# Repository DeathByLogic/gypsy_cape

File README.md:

# gypsy_cape
BeagleBone cape for the Gypsy robot.

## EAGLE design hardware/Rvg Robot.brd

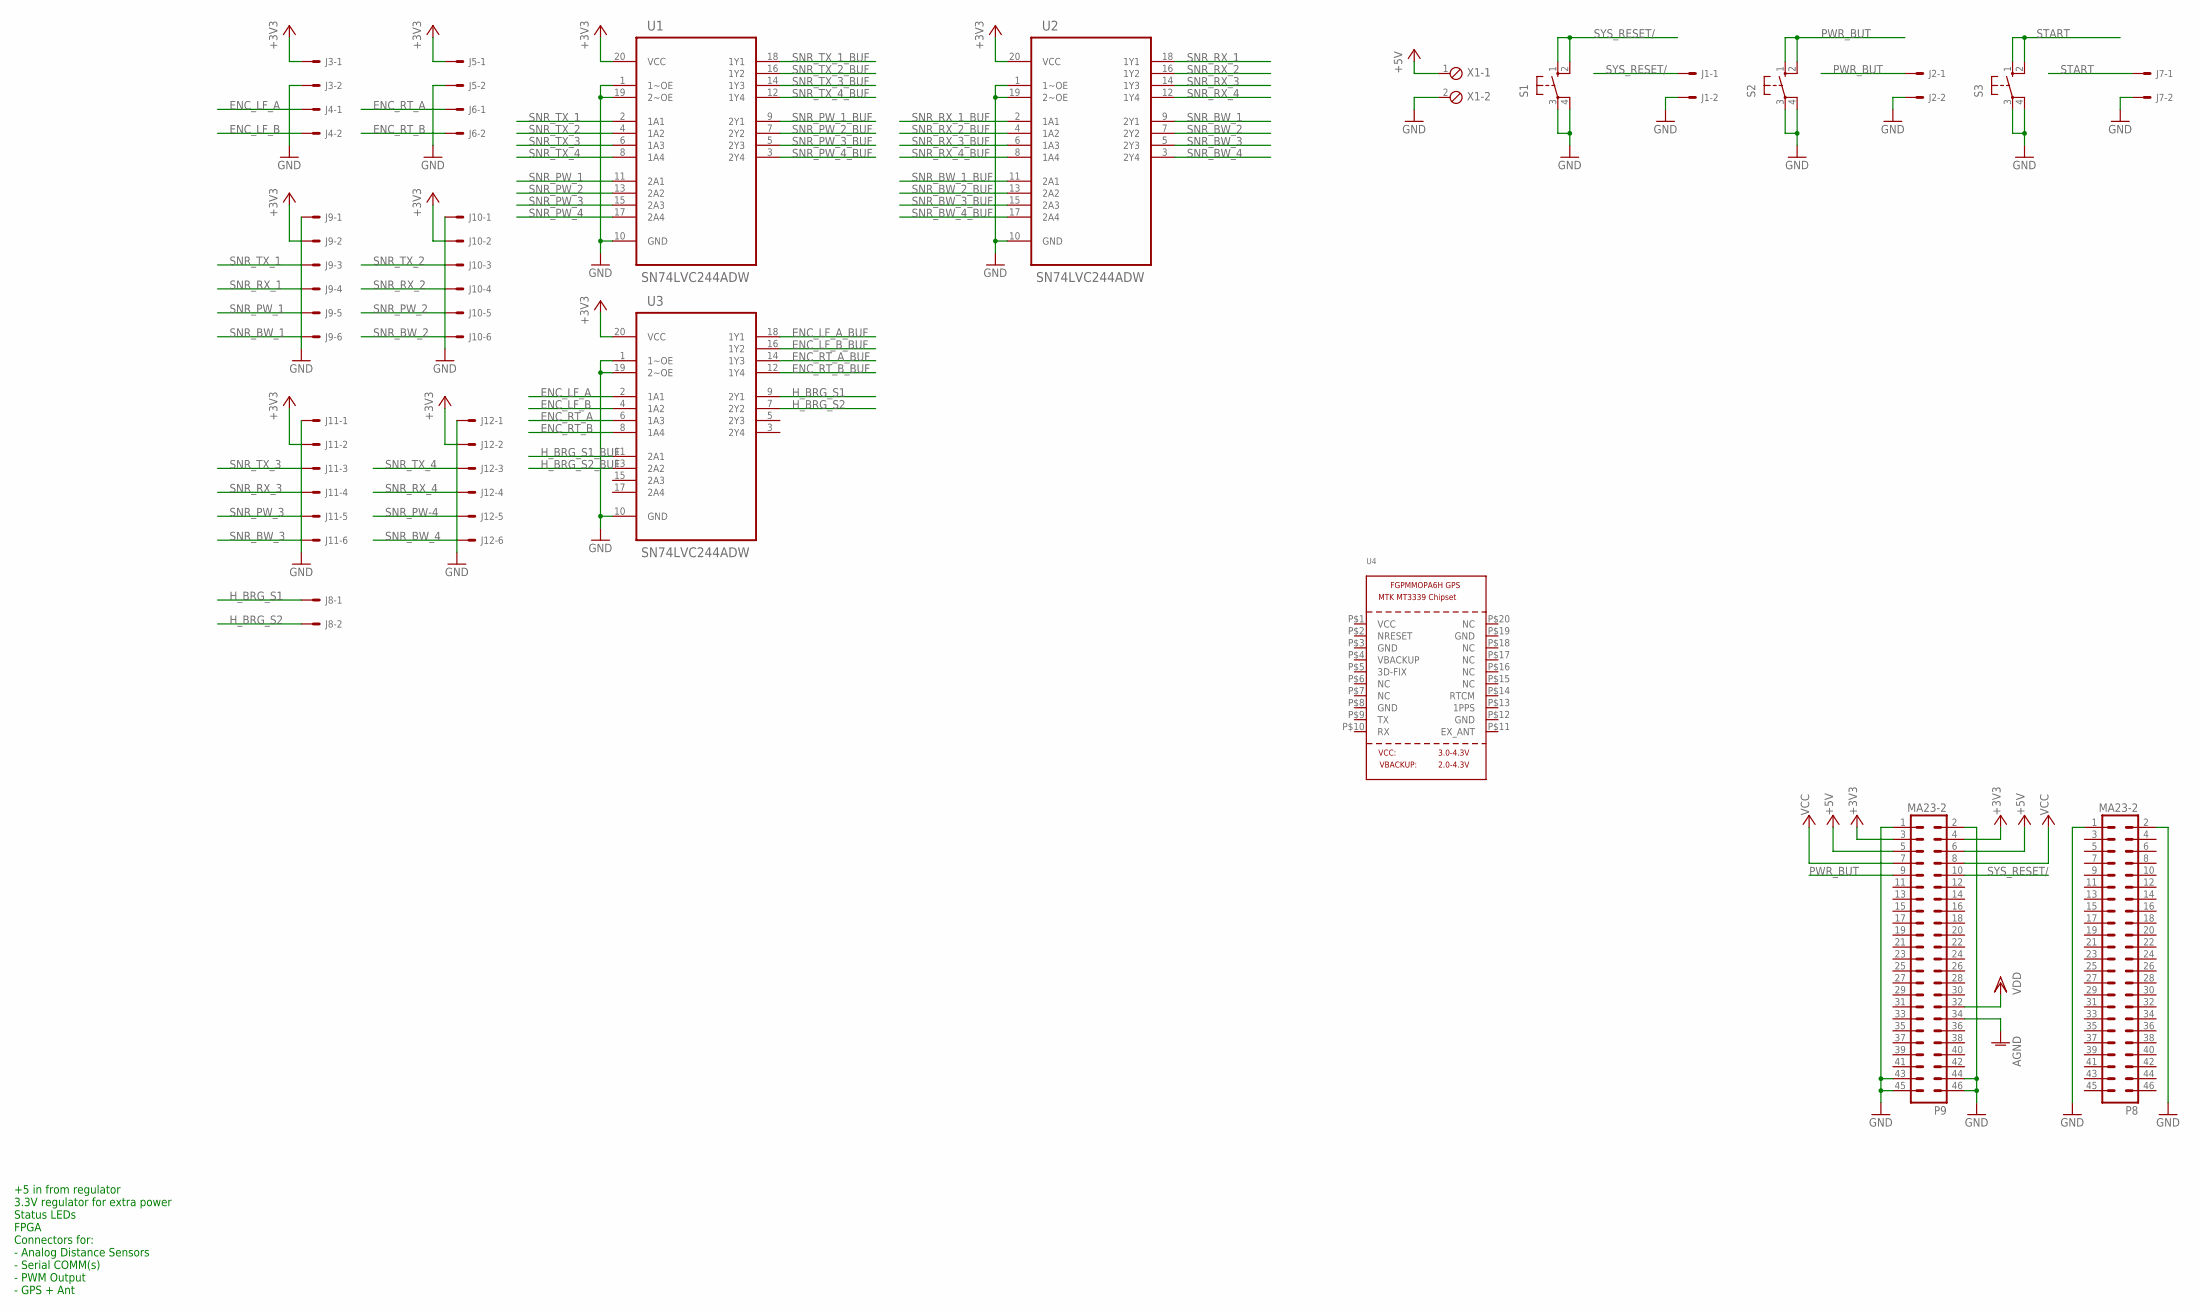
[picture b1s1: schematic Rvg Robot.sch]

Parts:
J1, J2, J3, J4, J5, J6, J7, J8: 22-27-2021-02; 6410-02
J9, J10, J11, J12: 22-27-2061-06; 6410-06
P8, P9: MA23-2
S1, S2, S3: 10-XX; B3F-10XX
U1, U2, U3: SN74LVC244ADW; SOIC127P1030X265-20N
U4: GPS_FGPMMOPA6H; FGPMMOPA6H
X1: MPT2; 2POL254

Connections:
+3V3: J3.1, J5.1, J9.2, J10.2, J11.2, J12.2, P9.3, P9.4, U1.20 (VCC), U2.20 (VCC), U3.20 (VCC)
+5V: P9.5, P9.6, X1.1
AGND: P9.34
ENC_LF_A: J4.1, U3.2 (1A1)
ENC_LF_A_BUF: U3.18 (1Y1)
ENC_LF_B: J4.2, U3.4 (1A2)
ENC_LF_B_BUF: U3.16 (1Y2)
ENC_RT_A: J6.1, U3.6 (1A3)
ENC_RT_A_BUF: U3.14 (1Y3)
ENC_RT_B: J6.2, U3.8 (1A4)
ENC_RT_B_BUF: U3.12 (1Y4)
GND: J1.2, J2.2, J3.2, J5.2, J7.2, J9.1, J10.1, J11.1, J12.1, P8.2, P9.1, P9.2, P9.43, P9.44, P9.45, P9.46, S1.3, S1.4 (P1), S2.3, S2.4 (P1), S3.3, S3.4 (P1), U1.1 (1~OE), U1.10 (GND), U1.19 (2~OE), U2.1 (1~OE), U2.10 (GND), U2.19 (2~OE), U3.1 (1~OE), U3.10 (GND), U3.19 (2~OE), X1.2
H_BRG_S1: J8.1, U3.9 (2Y1)
H_BRG_S1_BUF: U3.11 (2A1)
H_BRG_S2: J8.2, U3.7 (2Y2)
H_BRG_S2_BUF: U3.13 (2A2)
PWR_BUT: J2.1, P9.9, S2.1 (S), S2.2 (S1)
SNR_BW_1: J9.6, U2.9 (2Y1)
SNR_BW_1_BUF: U2.11 (2A1)
SNR_BW_2: J10.6, U2.7 (2Y2)
SNR_BW_2_BUF: U2.13 (2A2)
SNR_BW_3: J11.6, U2.5 (2Y3)
SNR_BW_3_BUF: U2.15 (2A3)
SNR_BW_4: J12.6, U2.3 (2Y4)
SNR_BW_4_BUF: U2.17 (2A4)
SNR_PW-4: J12.5
SNR_PW_1: J9.5, U1.11 (2A1)
SNR_PW_1_BUF: U1.9 (2Y1)
SNR_PW_2: J10.5, U1.13 (2A2)
SNR_PW_2_BUF: U1.7 (2Y2)
SNR_PW_3: J11.5, U1.15 (2A3)
SNR_PW_3_BUF: U1.5 (2Y3)
SNR_PW_4: U1.17 (2A4)
SNR_PW_4_BUF: U1.3 (2Y4)
SNR_RX_1: J9.4, U2.18 (1Y1)
SNR_RX_1_BUF: U2.2 (1A1)
SNR_RX_2: J10.4, U2.16 (1Y2)
SNR_RX_2_BUF: U2.4 (1A2)
SNR_RX_3: J11.4, U2.14 (1Y3)
SNR_RX_3_BUF: U2.6 (1A3)
SNR_RX_4: J12.4, U2.12 (1Y4)
SNR_RX_4_BUF: U2.8 (1A4)
SNR_TX_1: J9.3, U1.2 (1A1)
SNR_TX_1_BUF: U1.18 (1Y1)
SNR_TX_2: J10.3, U1.4 (1A2)
SNR_TX_2_BUF: U1.16 (1Y2)
SNR_TX_3: J11.3, U1.6 (1A3)
SNR_TX_3_BUF: U1.14 (1Y3)
SNR_TX_4: J12.3, U1.8 (1A4)
SNR_TX_4_BUF: U1.12 (1Y4)
START: J7.1, S3.1 (S), S3.2 (S1)
SYS_RESET/: J1.1, P9.10, S1.1 (S), S1.2 (S1)
VCC: P9.7, P9.8
VDD: P9.32

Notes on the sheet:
+5 in from regulator 3.3V regulator for extra power Status LEDs FPGA Connectors for: - Analog Distance Sensors - Serial COMM(s) - PWM Output - GPS + Ant

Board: 2 copper layers, 22 parts (0 on the bottom side), 28 nets, no tracks yet.

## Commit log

2013-09-21 Changed project folder name to Gypsy.
2015-03-27 Cleaned up cape project.
2018-09-30 Added device tree overlay files.
2018-09-30 Orginized files
